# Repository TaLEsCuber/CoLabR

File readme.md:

# CoLabR —— **Co**llaborate to write a **Lab** **R**eport.

*物理实验合作库（~~然而与 Google 的 colab 重名了~~），“R” 代表 “Report” ，即这个库主要用于存放与实验报告相关的内容（完整报告、数据和代码）。*

本仓库收录了我们在本科阶段所**合作**完成的四门物理实验课程的实验报告与相关资料。

它归属于我们的[实验报告分享项目](https://liuyinchu.github.io/labreport)。

---

以下是关于这个项目的说明。

您将在这里找到以下几类资源：

* **实验报告**：提供完整的实验报告成品（PDF 格式）与相应的 TeX 源码。
* **数据处理代码**：部分实验所使用的数据处理代码。
* **实验数据**：绝大部分实验的测量数据。
* **相关资料**：我们收集整理的一部分与实验相关的参考资料。

我们发起这个项目的初衷，可以归结为以下三点：

1.  **节约时间，提升效率**：我们深知实验课程中，报告格式的调整、实验原理的复述以及课后思考题的解答往往会耗费大量时间。希望我们的整理能为后来的学弟学妹们节约宝贵的精力，让大家能更专注于实验本身。
2.  **改善体验，激发兴趣**：希望这份小小的努力，能让大家在面对繁重的实验任务时，依然能感受到物理实验的乐趣，甚至能对未来选择实验物理作为研究方向产生些许积极的影响。
3.  **抛砖引玉，共同进步**：我们希望能以此抛砖引玉，激励更多有能力、有想法的同学，在我们的工作基础上进行更深层次的探索与创新，将这些基础实验开发出新的价值。

在您使用这些资源前，请务必仔细阅读以下注意事项：

1.  **关于实验报告**：报告的质量与完成时间大致呈正相关。早期的报告或有疏漏之处，若您想参考报告的行文结构与内容组织，建议从时间线靠后的报告看起。
2.  **关于 TeX 源码**：提供的源码主要用于参考与复制格式化内容（如表格、公式等），通常无法直接编译通过，敬请留意。
3.  **关于报告模板**：项目初期，我们使用了由 Huanyu Shi 学长创建的实验报告模板，在此表示感谢。后期我们在此模板基础上进行了二次开发，详情请参阅我们的相关项目主页。
4.  **关于代码**：仓库中的代码均为早期版本，可能已显陈旧。关于实验数据处理的更优实现，建议您关注我们的另一个专门项目。
5.  **关于数据**：请**不要**直接套用我们提供的实验数据来完成您自己的实验报告。一方面，这是严重的学术不端行为；另一方面，由于早期文件命名的极度不规范（对此我已进行深刻反思，并撰有随笔一篇，有兴趣可以来看看），您大概率也无法将数据与具体实验过程准确对应。更何况，所有纸质记录的原始数据均未包含在内。这些数据的预期使用方法是在您有兴趣的情况下找到对应数据来对比您的实验或增加数据量，达成所谓的“二次开发”。

---

本仓库中所有原创的实验报告及代码，其版权归原作者所有。其中的代码部分，您可自由使用。但**严禁抄袭、挪用实验报告中的任何实质性内容**。若因此产生任何学术诚信问题（比如被老师发现），后果由当事人自负，本分享项目概不负责（很重要，请注意）。项目中引用的部分参考资料，其版权归原始创作者所有。我们分享的初衷仅为学习交流。若您认为任何内容侵犯了您的合法权益，请立即与我们联系，我们将第一时间进行处理。

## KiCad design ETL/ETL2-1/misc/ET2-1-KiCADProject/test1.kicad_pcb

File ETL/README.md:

我们的电子技术实验报告质量普遍较差，因此这个仓库里只放一些稍微好一点的。

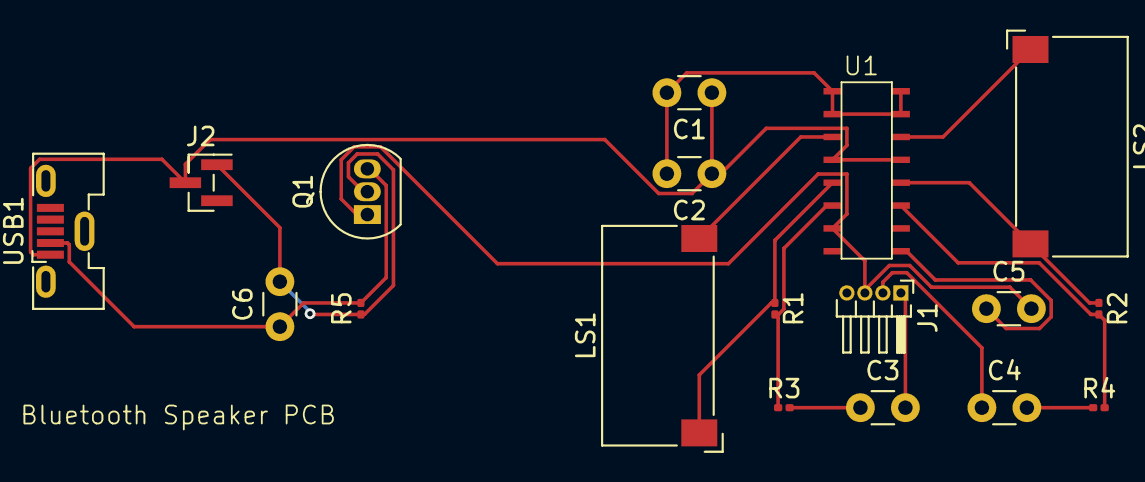
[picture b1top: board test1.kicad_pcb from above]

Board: 2 copper layers, 18 parts (0 on the bottom side), 16 nets.

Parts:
C1, C5: 0.1uF; C_Disc_D3.0mm_W1.6mm_P2.50mm
C2: 1000uF; C_Disc_D3.0mm_W1.6mm_P2.50mm
C3, C4: 1uF; C_Disc_D3.0mm_W1.6mm_P2.50mm
C6: 10uF; C_Disc_D3.0mm_W1.6mm_P2.50mm
J1: Conn_01x03_MountingPin; PinHeader_1x04_P1.00mm_Horizontal
J2: Conn_01x02_MountingPin; PinHeader_1x03_P1.00mm_Vertical_SMD_Pin1Right
LS1, LS2: Speaker; Speaker_CUI_CMR-1206S-67
Q1: BS108; TO-92_Inline
R1, R2, R5: 20K; R_0201_0603Metric
R3, R4: 4.7K; R_0201_0603Metric
U1: LM4863
USB1: USB_Micro-B_Molex-105133-0031

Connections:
GND: C5.2, J1.3, Q1.1 (D), U1.7 (GND)
unnamed: C3.1, R3.2
unnamed: C4.2, R4.1
unnamed: C3.2, J1.1
unnamed: C4.1, J1.2
unnamed: C6.2, J2.1, Q1.2 (G), R5.1
unnamed: C6.1, Q1.3 (S), R5.2, USB1.2 (-)
unnamed: C5.1, U1.8 (INL+), U1.9 (INR+), U1.10 (Bypass)
unnamed: C1.2, C2.2, U1.1 (SHDN), U1.2 (GND), U1.15 (GND), U1.16 (HP-IN)
unnamed: R1.2, R3.1, U1.6 (INL-)
unnamed: R2.2, R4.2, U1.11 (INR-)
unnamed: LS1.2, U1.3 (OUTL+)
unnamed: LS1.1, R1.1, U1.5 (OUTL-)
unnamed: LS2.1, U1.14 (OUTR+)
unnamed: LS2.2, R2.1, U1.12 (OUTR-)
VDD: C1.1, C2.1, J2.2, U1.4 (VDD), U1.13 (VDD), USB1.1 (+)

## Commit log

2024-09-09 合并ETLabR和DExp_Sam
2024-09-09 添加了项目流程管理文件
2024-09-09 添加了关于近代物理实验的文件夹并且修改了设计性实验的命名
2024-09-10 something strange happened
2024-09-10 something strange happened again
2024-09-11 Debug
2024-09-12 请仔细阅读/ETLabR/ET-template/directions.md，详细了解电子技术实验2的整个实验文件规范
2024-09-19 完成了预习报告
2024-09-23 更新了流程管理及各种说明文件
2024-09-24 上传了实验数据，全部存放在data文件夹中，具体请看data/directions文件。
2024-09-25 对实验数据进行了命名
2024-09-25 整理了电子技术实验报告第一次写的计划
2024-09-25 上传了两张音响的成品图
2024-09-27 上传了量子密钥分发实验的相关数据
2024-09-27 添加了相关代码
2024-09-29 the semi-finished KiCADProject has been uploaded
2024-09-29 完成了ET2-1的部分内容
2024-09-30 进一步完成了ET2-1的部分内容
2024-09-30 基本完成了ET2-1
2024-10-01 完成了PCB版的绘制。实验报告完成了“焊接的流程”、“difficulties”、“conclusion”、“summary”
2024-10-10 上传APL1-1
2024-10-10 修改了命名
2024-10-11 上传实验数据
2024-10-11 强调及时上传数据的重要性
2024-10-18 上传D8实验数据的压缩包
2024-10-19 上传老师签字的原始数据
2024-10-19 以将实验一的数据敲成excel表格，实验二三四均有直接导出的excel
2024-10-24 上传问题总结
2024-10-24 上传马万成的签名图片
2024-10-24 上传谐振腔调节心得
2024-10-25 上传锁相放大器第二次实验的原始数据
2024-10-25 上传锁相放大器第二次实验的纸质数据记录
2024-10-28 上传基本完成了的APL1-8，请分发给大家阅读和修改，预计时间一天，更多内容见Issue
2024-10-28 锁相放大器第二次实验的有关数据已解压
2024-10-31 完善了D8实验报告的一些小问题，包括思考题、成员签名、排版等
2024-10-31 修改了表头中的学生姓名、学号等信息
2024-11-01 上传D4相关实验数据
2024-11-07 上传APL1-1-A代码，请将数据包打包为zip
2024-11-07 上传1.6的实验数据
2024-11-08 上传D5和D6的实验数据
2024-11-12 上传APL1-4数据处理和预习报告
2024-11-14 上传D4的实验报告
2024-11-20 上传APL1-5+6数据处理
2024-12-04 已上传电子技术实验相关数据
2024-12-18 已上传所有关于高速遮光器的实验数据和代码
2024-12-25 上传纸质版原始数据
2024-12-25 上传光谱和质谱的相关图片
2024-12-26 上传D2的实验一的数据表格
2025-01-10 完成测量放大器的实验报告
2025-03-25 (CoLabR)win -> github: upload the ET2-3.zip (20250325)
2025-03-25 (CoLabR)win -> github: update the branch main, and creat the branch dev2. (20250325)
2025-03-25 (CoLabR)win -> github: update the dev2. (20250325)
2025-03-27 (CoLabR)Win -> Github: upload the necessary file of apl2-5. (20250327)
2025-07-21 (CoLabR)Win->Github: Organized this GitHub repository, 20250722.
